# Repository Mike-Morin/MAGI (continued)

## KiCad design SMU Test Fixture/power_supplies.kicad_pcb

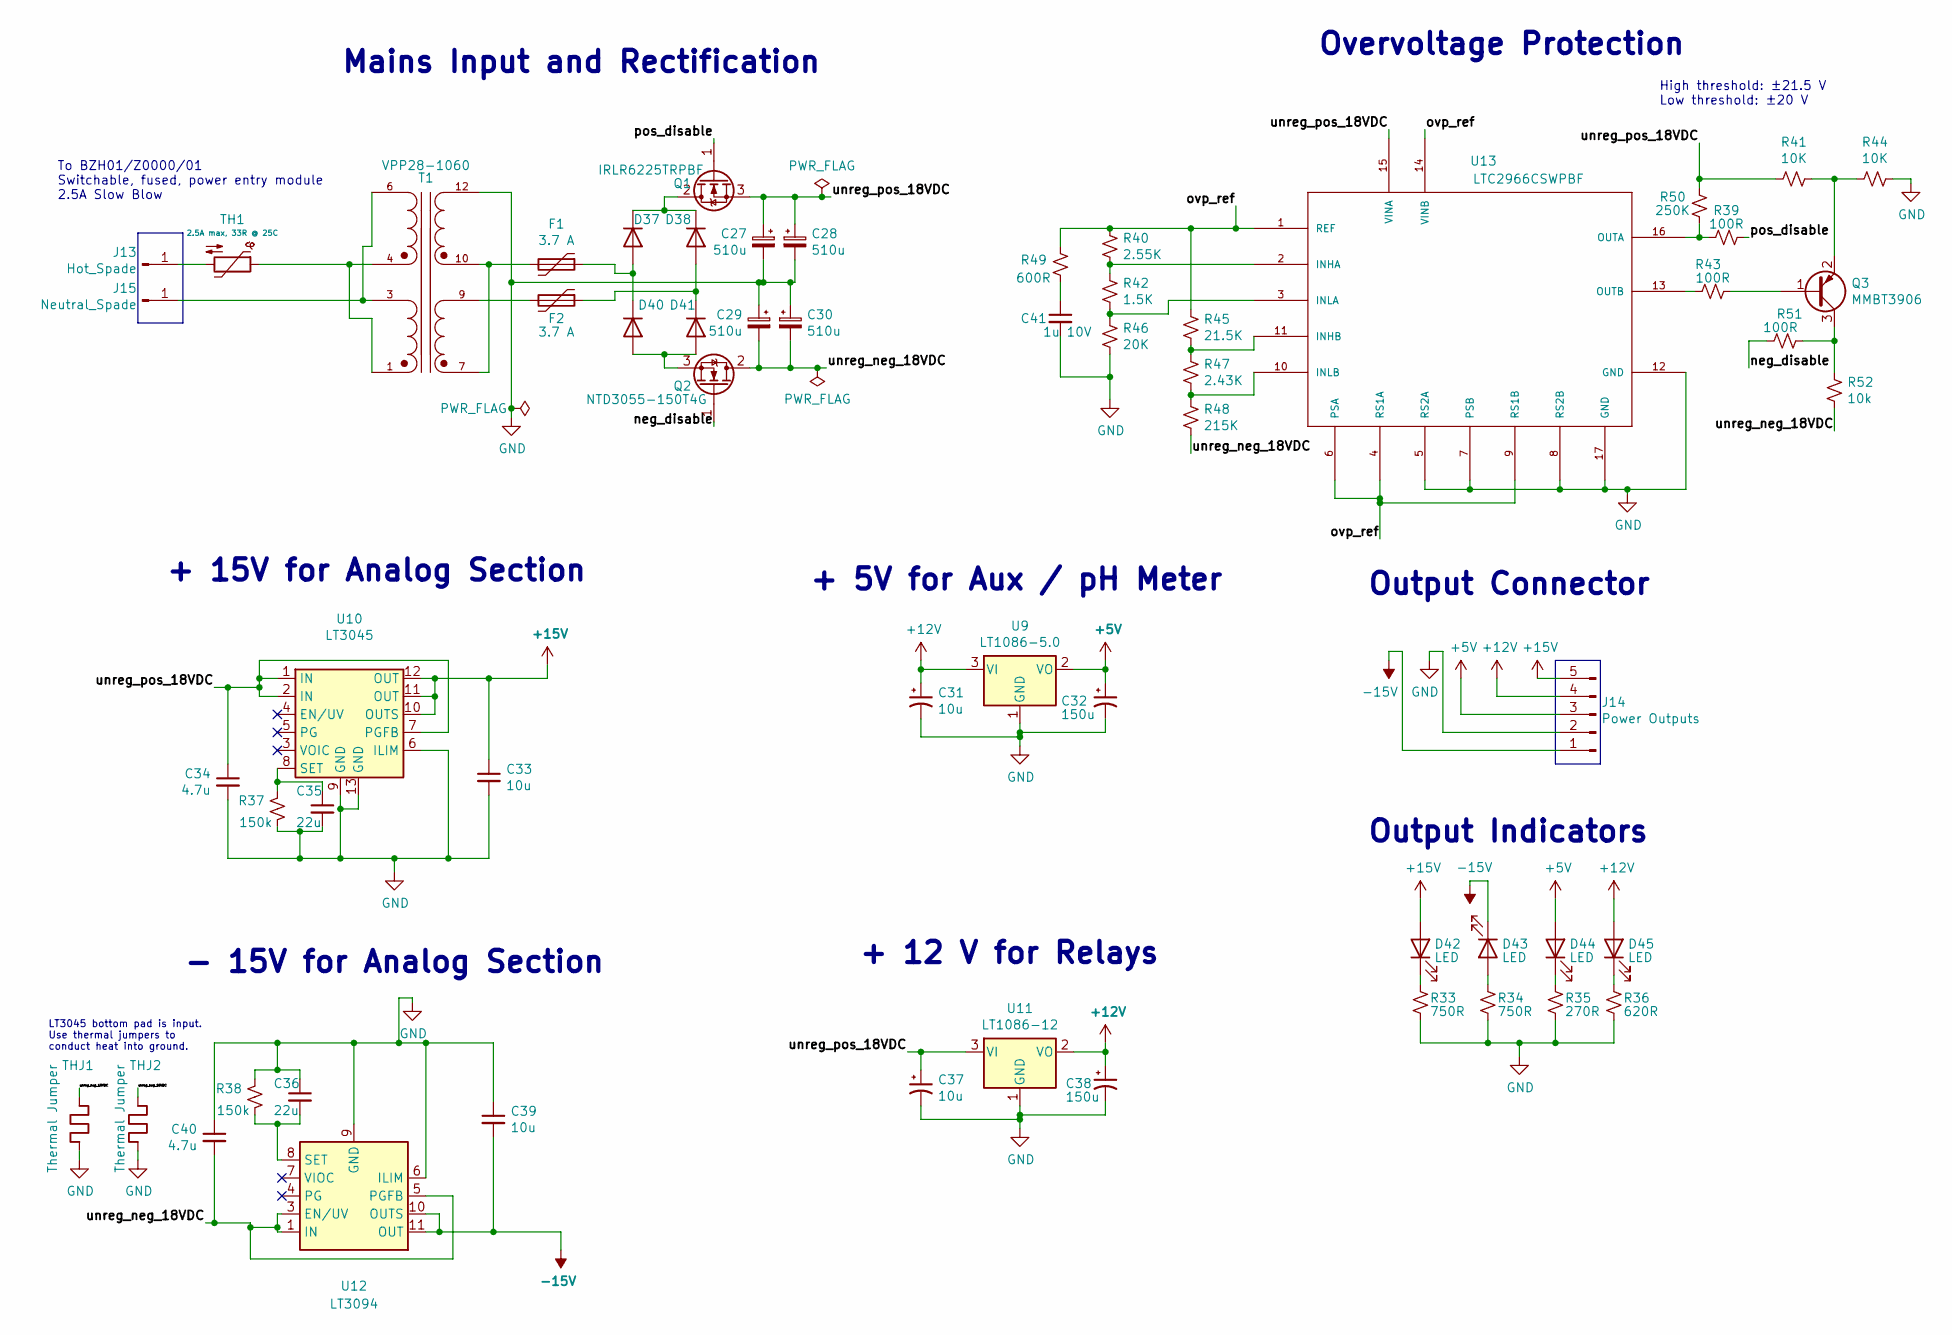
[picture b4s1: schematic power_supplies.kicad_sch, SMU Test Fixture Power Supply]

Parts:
C27, C28, C29, C30: 510u; CP_Elec_18x22
C31, C37: 10u; CP_Elec_6.3x5.8
C32, C38: 150u; CP_Elec_10x10
C33, C39: 10u; C_0805_2012Metric_Pad1.18x1.45mm_HandSolder_Kelvin
C34, C40: 4.7u; C_0805_2012Metric_Pad1.18x1.45mm_HandSolder
C35, C36: 22u; C_0805_2012Metric_Pad1.18x1.45mm_HandSolder
C41: 1u 10V; C_0603_1608Metric_Pad1.08x0.95mm_HandSolder
D37, D38, D40, D41: D; TO-263-2
D42, D43, D44, D45: LED; LED_D3.0mm_Horizontal_O6.35mm_Z2.0mm
F1, F2: 3.7 A; Fuse_2920_7451Metric_Pad2.10x5.45mm_HandSolder
J13: Hot_Spade; p250_spade
J14: Power Outputs; PinHeader_1x05_P2.54mm_Horizontal
J15: Neutral_Spade; p250_spade
Q1: IRLR6225TRPBF; TO-252-2
Q2: NTD3055-150T4G; TO-252-2
Q3: MMBT3906; SOT-23
R33, R34: 750R; R_0805_2012Metric_Pad1.20x1.40mm_HandSolder
R35: 270R; R_0805_2012Metric_Pad1.20x1.40mm_HandSolder
R36: 620R; R_0805_2012Metric_Pad1.20x1.40mm_HandSolder
R37, R38: 150k; R_0805_2012Metric_Pad1.20x1.40mm_HandSolder
R39, R43, R51: 100R; R_0603_1608Metric_Pad0.98x0.95mm_HandSolder
R40: 2.55K; R_0603_1608Metric_Pad0.98x0.95mm_HandSolder
R41, R44: 10K; R_0603_1608Metric_Pad0.98x0.95mm_HandSolder
R42: 1.5K; R_0603_1608Metric_Pad0.98x0.95mm_HandSolder
R45: 21.5K; R_0603_1608Metric_Pad0.98x0.95mm_HandSolder
R46: 20K; R_0603_1608Metric_Pad0.98x0.95mm_HandSolder
R47: 2.43K; R_0603_1608Metric_Pad0.98x0.95mm_HandSolder
R48: 215K; R_0603_1608Metric_Pad0.98x0.95mm_HandSolder
R49: 600R; R_0603_1608Metric_Pad0.98x0.95mm_HandSolder
R50: 250K; R_0603_1608Metric_Pad0.98x0.95mm_HandSolder
R52: 10k; R_0603_1608Metric_Pad0.98x0.95mm_HandSolder
T1: VPP28-1060; XFMR_VPP28-1060
TH1: 2.5A max, 33R @ 25C; NTC d=15 p=7p5mm w=7mm
THJ1, THJ2: Thermal Jumper; C_0805_2012Metric_Pad1.18x1.45mm_HandSolder
U9: LT1086-5.0; TO-220-3_Vertical
U10: LT3045; MSOP-12-1EP_3x4mm_P0.65mm_EP1.65x2.85mm
U11: LT1086-12; TO-220-3_Vertical
U12: LT3094; MSOP-12-1EP_3x4mm_P0.65mm_EP1.65x2.85mm
U13: LTC2966CSWPBF; QFN-16-1EP_3x3mm_P0.5mm_EP1.45x1.45mm; MANUFACTURER_PART_NUMBER ltc2966csw#pbf

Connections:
+5V: C32.1, D44.2 (A), J14.3, U9.2 (VO)
+12V: C31.1, C38.1, D45.2 (A), J14.4, U9.3 (VI), U11.2 (VO)
+15V: C33.1, D42.2 (A), J14.5, U10.10 (OUTS), U10.11 (OUT), U10.12 (OUT)
-15V: C39.2, D43.1 (K), J14.1, U12.10 (OUTS), U12.11 (OUT), U12.12 (OUT)
/neg_disable: Q2.1 (G), R51.2
/ovp_ref: R40.1, R45.1, R49.1, U13.1 (REF), U13.4 (RS1A), U13.6 (PSA), U13.9 (RS1B), U13.14 (VINB)
/pos_disable: Q1.1 (G), R39.1
/unreg_neg_18VDC: C29.2, C30.2, C40.2, Q2.2 (D), R48.2, R52.2, THJ1.1, THJ2.1, U12.1 (IN), U12.2 (IN), U12.3 (EN/UV), U12.5 (PGFB), U12.13 (IN)
/unreg_pos_18VDC: C27.1, C28.1, C34.1, C37.1, Q1.3 (S), R41.2, R50.1, U10.1 (IN), U10.2 (IN), U10.7 (PGFB), U11.3 (VI), U13.15 (VINA)
GND: C27.2, C28.2, C29.1, C30.1, C31.2, C32.2, C33.2, C34.2, C35.2, C36.1, C37.2, C38.2, C39.1, C40.1, C41.2, J14.2, R33.2, R34.2, R35.2, R36.2, R37.2, R38.1, R44.1, R46.2, T1.12, THJ1.2, THJ2.2, U9.1 (GND), U10.6 (ILIM), U10.9 (GND), U10.13 (GND), U11.1 (GND), U12.6 (ILIM), U12.9 (GND), U13.5 (RS2A), U13.7 (PSB), U13.8 (RS2B), U13.12 (GND), U13.17 (GND)
unnamed: C35.1, R37.1, U10.8 (SET)
unnamed: C36.2, R38.2, U12.8 (SET)
unnamed: C41.1, R49.2
unnamed: D37.1 (K), D38.1 (K), Q1.2 (D)
unnamed: D37.2 (A), D40.1 (K), F1.1
unnamed: D38.2 (A), D41.1 (K), F2.1
unnamed: D40.2 (A), D41.2 (A), Q2.3 (S)
unnamed: D42.1 (K), R33.1
unnamed: D43.2 (A), R34.1
unnamed: D44.1 (K), R35.1
unnamed: D45.1 (K), R36.1
unnamed: F1.2, T1.7, T1.10
unnamed: F2.2, T1.9
unnamed: J13.1, TH1.2
unnamed: J15.1, T1.3, T1.6
unnamed: Q3.1 (B), R43.2
unnamed: Q3.2 (E), R41.1, R44.2
unnamed: Q3.3 (C), R51.1, R52.1
unnamed: R39.2, R50.2, U13.16 (OUTA)
unnamed: R40.2, R42.1, U13.2 (INHA)
unnamed: R42.2, R46.1, U13.3 (INLA)
unnamed: R43.1, U13.13 (OUTB)
unnamed: R45.2, R47.1, U13.11 (INHB)
unnamed: R47.2, R48.1, U13.10 (INLB)
unnamed: T1.1, T1.4, TH1.1

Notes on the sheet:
LT3045 bottom pad is input. Use thermal jumpers to conduct heat into ground.
Overvoltage Protection
+ 5V for Aux / pH Meter
Output Indicators
To BZH01/Z0000/01 Switchable, fused, power entry module 2.5A Slow Blow
- 15V for Analog Section
Mains Input and Rectification
+ 12 V for Relays
+ 15V for Analog Section
Output Connector
High threshold: ±21.5 V Low threshold: ±20 V

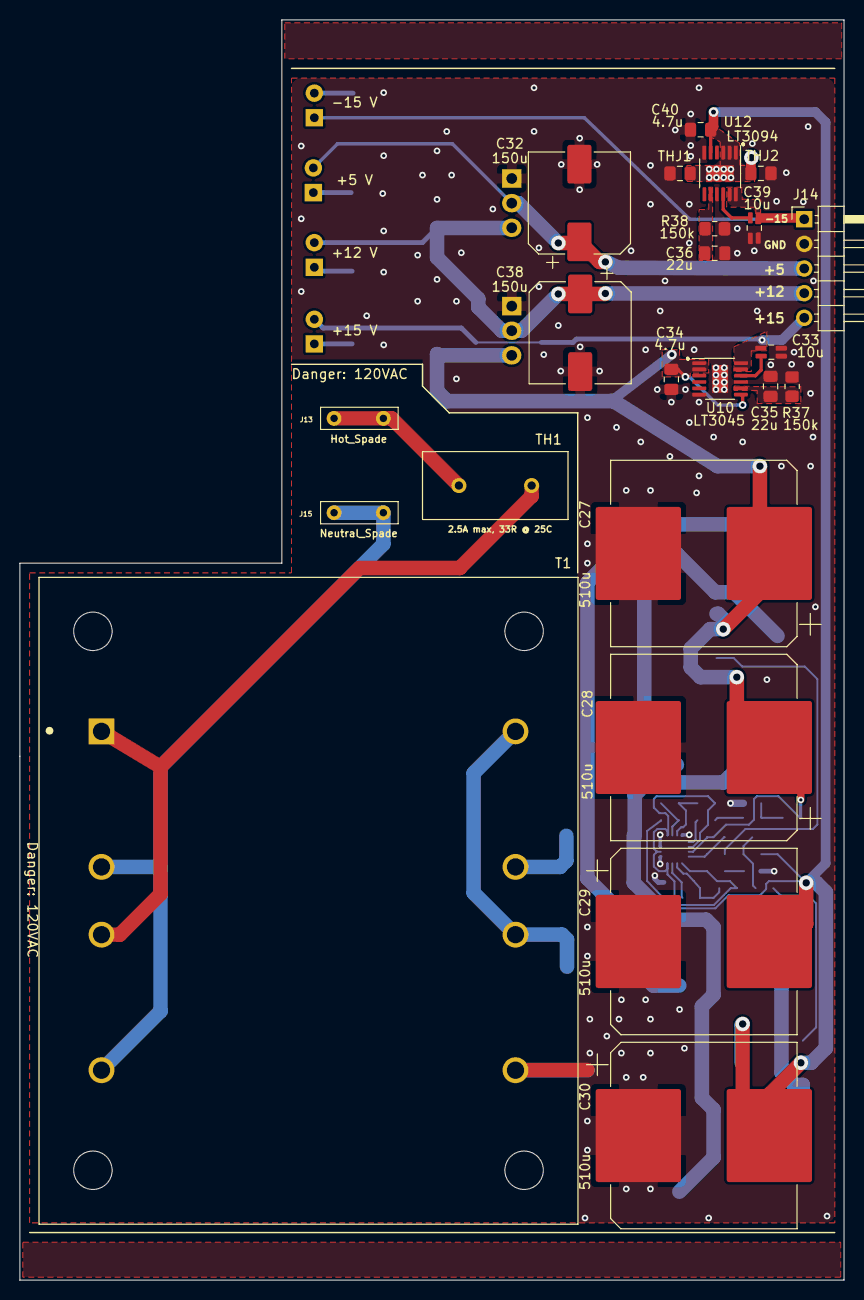
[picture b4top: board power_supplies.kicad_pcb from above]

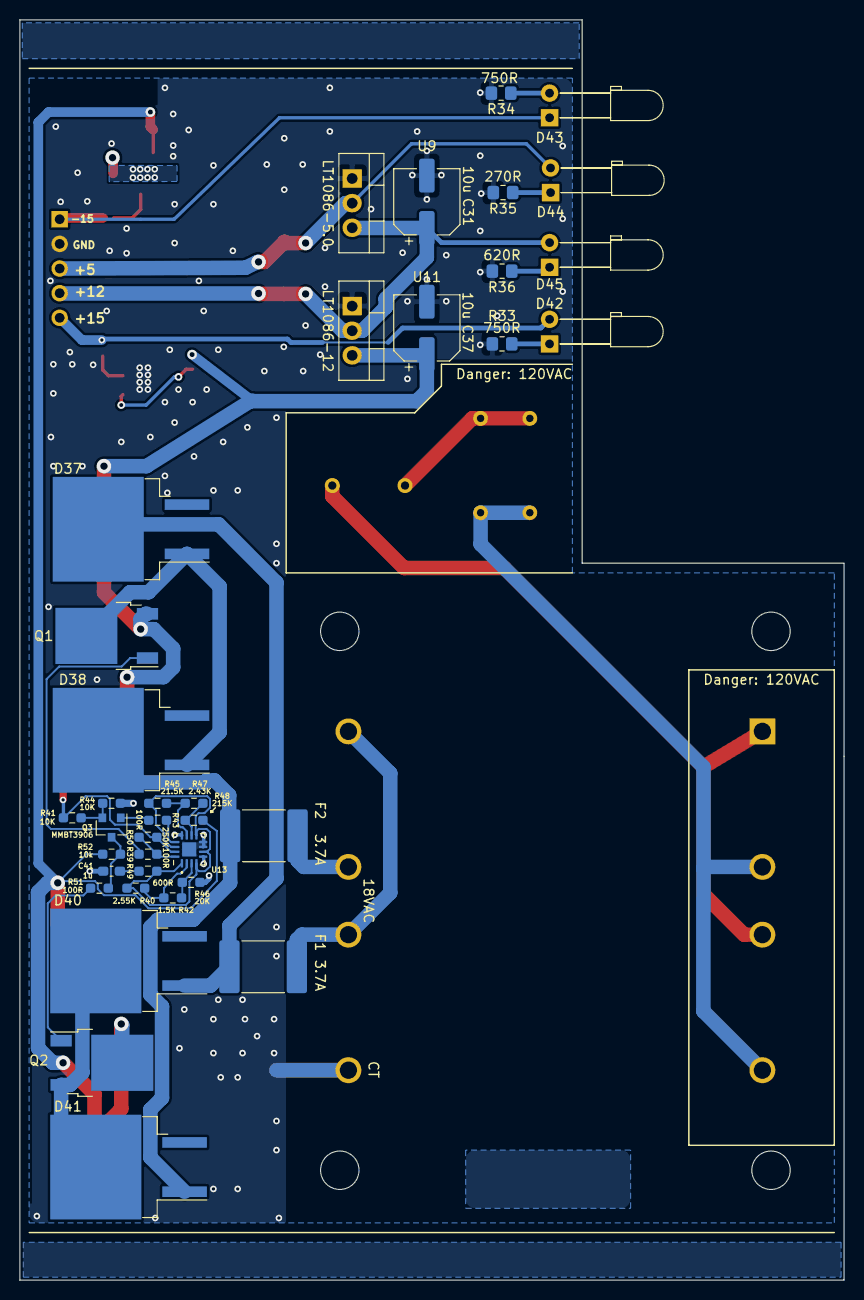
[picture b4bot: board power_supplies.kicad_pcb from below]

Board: 2 copper layers, 84.9 x 129.9 mm, 60 parts (37 on the bottom side), 35 nets.

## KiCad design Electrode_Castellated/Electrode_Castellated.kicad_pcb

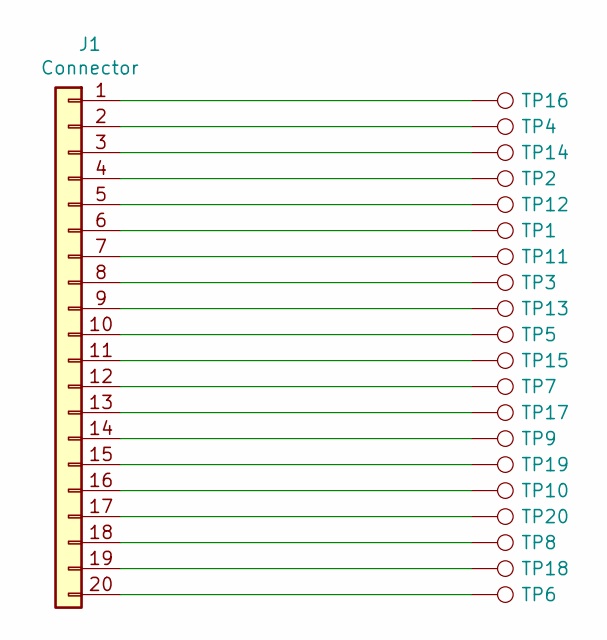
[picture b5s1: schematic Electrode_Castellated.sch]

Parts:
J1: Connector; Millmax Pad Contacts
TP1: 6; TestPoint_THTPad_D2.0mm_Drill1.0mm
TP2: 4; TestPoint_THTPad_D2.0mm_Drill1.0mm
TP3: 8; TestPoint_THTPad_D2.0mm_Drill1.0mm
TP4: 2; TestPoint_THTPad_D2.0mm_Drill1.0mm
TP5: 10; TestPoint_THTPad_D2.0mm_Drill1.0mm
TP6: 30; TestPoint_THTPad_D2.0mm_Drill1.0mm
TP7: 12; TestPoint_THTPad_D2.0mm_Drill1.0mm
TP8: 18; TestPoint_THTPad_D2.0mm_Drill1.0mm
TP9: 14; TestPoint_THTPad_D2.0mm_Drill1.0mm
TP10: 16; TestPoint_THTPad_D2.0mm_Drill1.0mm
TP11: 7; TestPoint_THTPad_D2.0mm_Drill1.0mm
TP12: 5; TestPoint_THTPad_D2.0mm_Drill1.0mm
TP13: 9; TestPoint_THTPad_D2.0mm_Drill1.0mm
TP14: 3; TestPoint_THTPad_D2.0mm_Drill1.0mm
TP15: 11; TestPoint_THTPad_D2.0mm_Drill1.0mm
TP16: 1; TestPoint_THTPad_D2.0mm_Drill1.0mm
TP17: 13; TestPoint_THTPad_D2.0mm_Drill1.0mm
TP18: 19; TestPoint_THTPad_D2.0mm_Drill1.0mm
TP19: 15; TestPoint_THTPad_D2.0mm_Drill1.0mm
TP20: 17; TestPoint_THTPad_D2.0mm_Drill1.0mm

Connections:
unnamed: J1.1, TP16.1
unnamed: J1.2, TP4.1
unnamed: J1.3, TP14.1
unnamed: J1.4, TP2.1
unnamed: J1.5, TP12.1
unnamed: J1.6, TP1.1
unnamed: J1.7, TP11.1
unnamed: J1.8, TP3.1
unnamed: J1.9, TP13.1
unnamed: J1.10, TP5.1
unnamed: J1.11, TP15.1
unnamed: J1.12, TP7.1
unnamed: J1.13, TP17.1
unnamed: J1.14, TP9.1
unnamed: J1.15, TP19.1
unnamed: J1.16, TP10.1
unnamed: J1.17, TP20.1
unnamed: J1.18, TP8.1
unnamed: J1.19, TP18.1
unnamed: J1.20, TP6.1

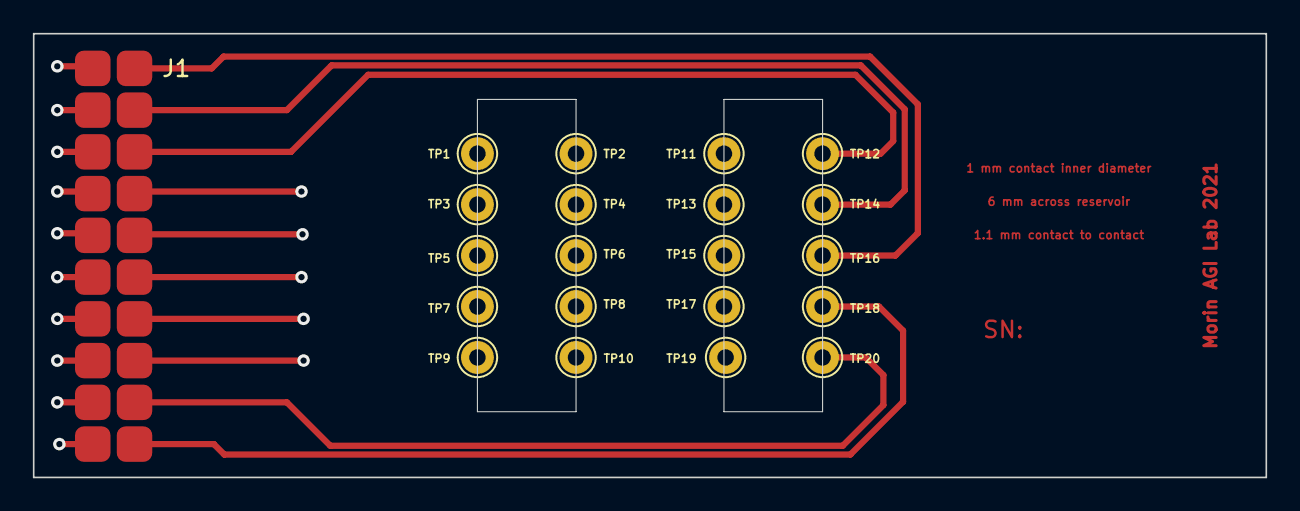
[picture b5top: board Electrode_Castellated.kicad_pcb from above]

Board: 4 copper layers, 75.0 x 27.0 mm, 21 parts (0 on the bottom side), 20 nets.

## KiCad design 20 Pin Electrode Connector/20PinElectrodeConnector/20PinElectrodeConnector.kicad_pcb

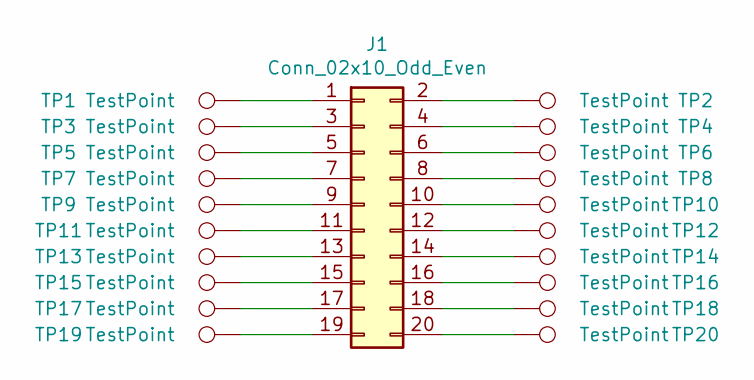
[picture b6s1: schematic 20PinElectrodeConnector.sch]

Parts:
J1: Conn_02x10_Odd_Even; Millimax_817-22-020-30-001101
TP1, TP2, TP3, TP4, TP5, TP6, TP7, TP8, TP9, TP10, TP11, TP12, TP13, TP14, TP15, TP16, TP17, TP18, TP19, TP20: TestPoint; SolderWire-0.25sqmm_1x01_D0.65mm_OD2mm

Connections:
unnamed: J1.1, TP1.1
unnamed: J1.2, TP2.1
unnamed: J1.3, TP3.1
unnamed: J1.4, TP4.1
unnamed: J1.5, TP5.1
unnamed: J1.6, TP6.1
unnamed: J1.7, TP7.1
unnamed: J1.8, TP8.1
unnamed: J1.9, TP9.1
unnamed: J1.10, TP10.1
unnamed: J1.11, TP11.1
unnamed: J1.12, TP12.1
unnamed: J1.13, TP13.1
unnamed: J1.14, TP14.1
unnamed: J1.15, TP15.1
unnamed: J1.16, TP16.1
unnamed: J1.17, TP17.1
unnamed: J1.18, TP18.1
unnamed: J1.19, TP19.1
unnamed: J1.20, TP20.1

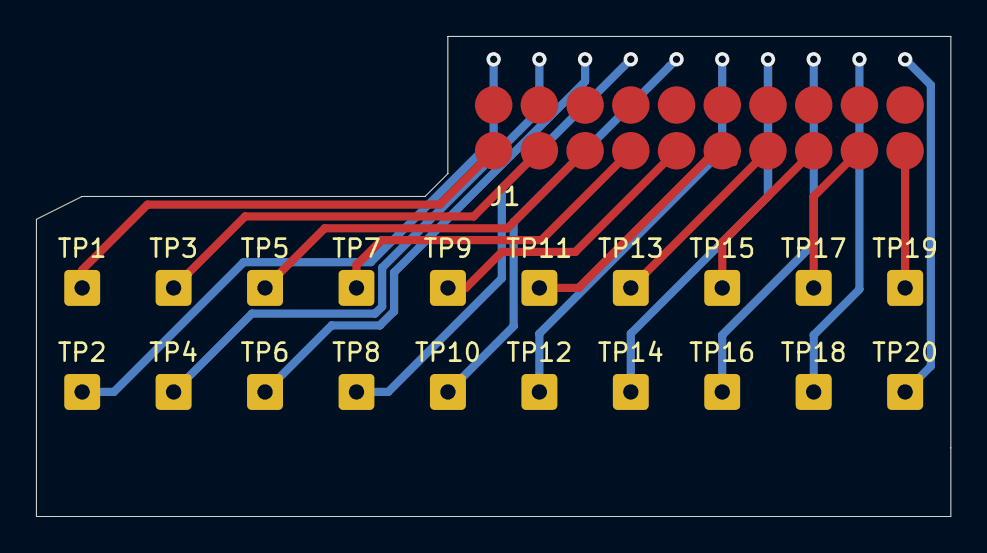
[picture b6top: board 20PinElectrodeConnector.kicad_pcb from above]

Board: 2 copper layers, 50.8 x 26.7 mm, 21 parts (0 on the bottom side), 20 nets.

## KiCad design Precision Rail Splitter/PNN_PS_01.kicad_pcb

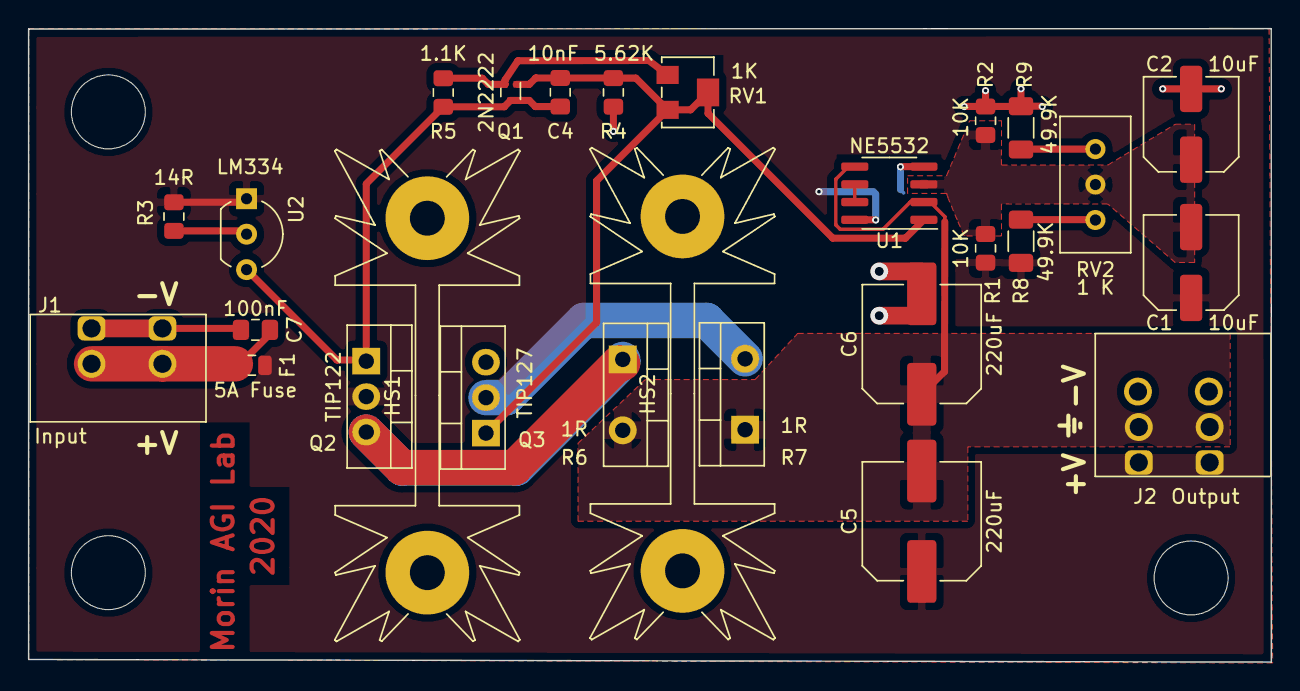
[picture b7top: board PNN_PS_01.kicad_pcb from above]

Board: 2 copper layers, 89.1 x 45.4 mm, 31 parts (1 on the bottom side), 14 nets.

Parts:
C1, C2: 10uF; C_Elec_6.3x5.8
C3, C7: 100nF; C_0805_2012Metric_Pad1.18x1.45mm_HandSolder
C4: 10nF; C_0805_2012Metric_Pad1.15x1.40mm_HandSolder
C5, C6: 220uF; C_Elec_8x10.2
F1: 5A Fuse; Fuse_0805_2012Metric
H1, H2, H3: MountingHole; MountingHole_5.3mm_M5_ISO14580
HS1, HS2: Heatsink; courtyardfix_Heatsink_Fischer_SK104-STC-STIC_35x13mm_2xDril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
J1: Input; EM274202H
J2: Output; EM274203H
Q1: 2N2222; SOT-723
Q2: TIP122; TO-220-3_Vertical
Q3: TIP127; TO-220-3_Vertical
R1, R2: 10K; R_0805_2012Metric_Pad1.15x1.40mm_HandSolder
R3: 14R; R_0805_2012Metric_Pad1.15x1.40mm_HandSolder
R4: 5.62K; R_0805_2012Metric_Pad1.15x1.40mm_HandSolder
R5: 1.1K; R_0805_2012Metric_Pad1.15x1.40mm_HandSolder
R6, R7: 1R; TO-220-2_Vertical
R8, R9: 49.9K; R_1206_3216Metric_Pad1.30x1.75mm_HandSolder
RV1: 1K; Potentiometer_Bourns_3214W_Vertical
RV2: 1 K; Potentiometer_Bourns_3296W_Vertical
U1: NE5532; SOIC-8_3.9x4.9mm_P1.27mm
U2: LM334; TO-92_Inline_Wide

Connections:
+9V: C1.1, C3.1, C5.1, F1.2, J2.1, Q2.2, R1.1, R3.1, R8.1, U1.8, U2.1
-9V: C2.2, C3.2, C6.2, C7.1, J1.1, J2.3, Q3.3, R2.2, R4.2, R9.2, U1.4
GND: C5.2, C6.1, J2.2, R6.2, R7.1, U1.2, U1.5
unnamed: C1.2, C2.1, R1.2, R2.1, RV2.2, U1.3
unnamed: C4.1, Q1.3, Q2.1, R5.1, U2.3
unnamed: C4.2, Q1.1, Q3.1, R4.1, RV1.2, RV1.3, U1.1
unnamed: C7.2, F1.1, J1.2
unnamed: Q1.2, R5.2, RV1.1
unnamed: Q2.3, R6.1
unnamed: Q3.2, R7.2
unnamed: R3.2, U2.2
unnamed: R8.2, RV2.1
unnamed: R9.1, RV2.3
unnamed: U1.6, U1.7

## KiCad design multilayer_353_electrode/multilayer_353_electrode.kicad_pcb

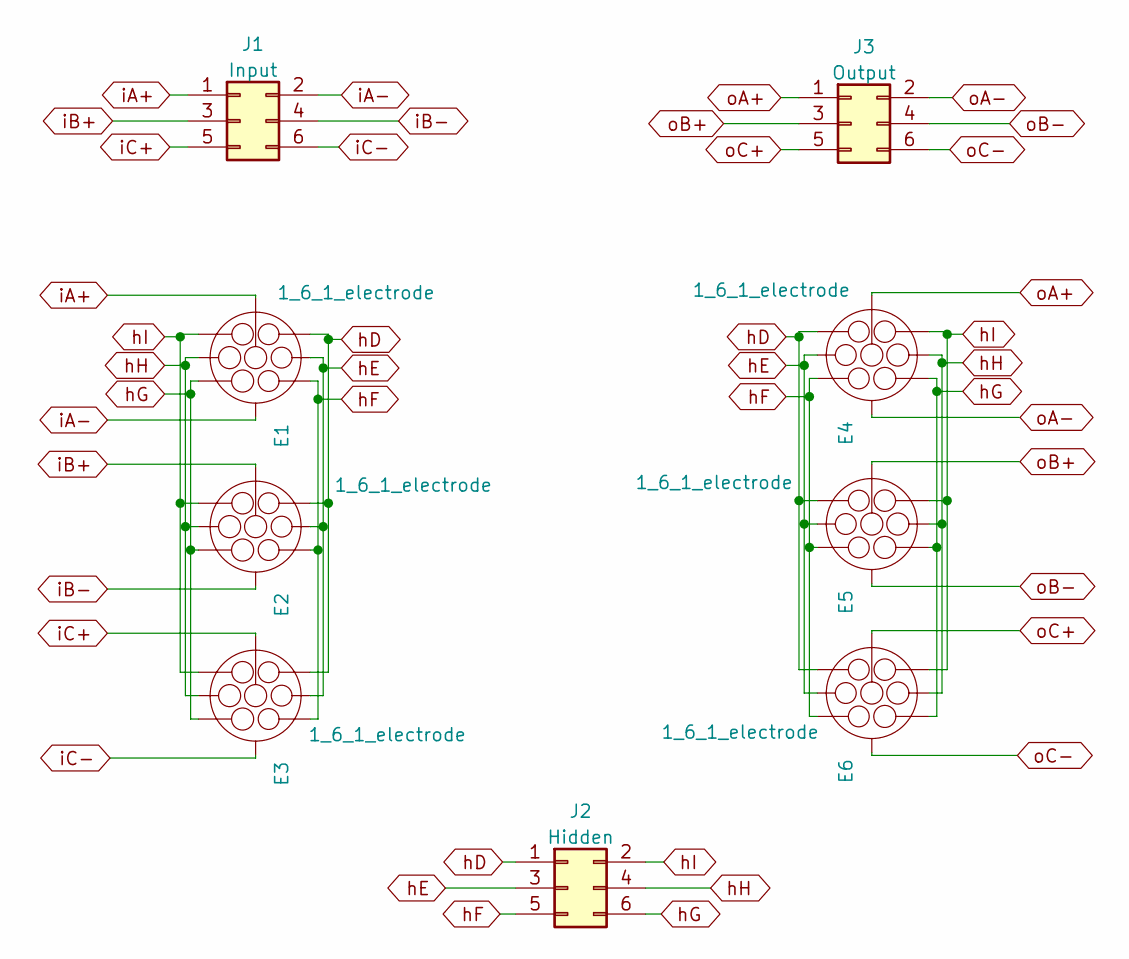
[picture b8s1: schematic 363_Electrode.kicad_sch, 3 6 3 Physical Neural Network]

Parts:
E1, E2, E3, E4, E5, E6: 1_6_1_electrode
J1: Input; PinHeader_2x03_P2.54mm_Vertical_SMD
J2: Hidden; PinHeader_2x03_P2.54mm_Vertical_SMD
J3: Output; PinHeader_2x03_P2.54mm_Vertical_SMD

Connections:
hD: E1.7 (H6), E2.7 (H6), E3.7 (H6), E4.7 (H6), E5.7 (H6), E6.7 (H6), J2.1
hE: E1.2 (H1), E2.2 (H1), E3.2 (H1), E4.2 (H1), E5.2 (H1), E6.2 (H1), J2.3
hF: E1.3 (H2), E2.3 (H2), E3.3 (H2), E4.3 (H2), E5.3 (H2), E6.3 (H2), J2.5
hG: E1.4 (H3), E2.4 (H3), E3.4 (H3), E4.4 (H3), E5.4 (H3), E6.4 (H3), J2.6
hH: E1.5 (H4), E2.5 (H4), E3.5 (H4), E4.5 (H4), E5.5 (H4), E6.5 (H4), J2.4
hI: E1.6 (H5), E2.6 (H5), E3.6 (H5), E4.6 (H5), E5.6 (H5), E6.6 (H5), J2.2
iA+: E1.1 (C), J1.1
iA-: E1.8 (R), J1.2
iB+: E2.1 (C), J1.3
iB-: E2.8 (R), J1.4
iC+: E3.1 (C), J1.5
iC-: E3.8 (R), J1.6
oA+: E4.1 (C), J3.1
oA-: E4.8 (R), J3.2
oB+: E5.1 (C), J3.3
oB-: E5.8 (R), J3.4
oC+: E6.1 (C), J3.5
oC-: E6.8 (R), J3.6

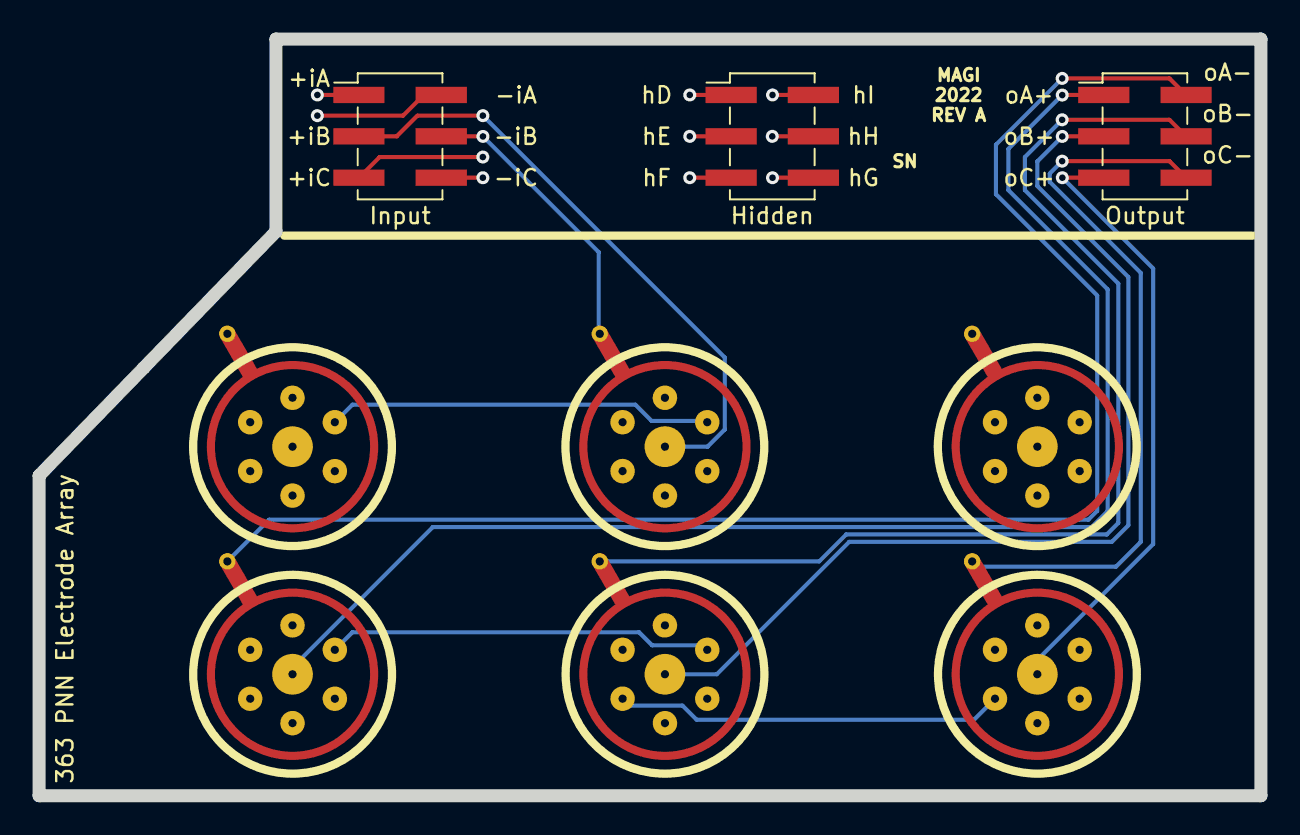
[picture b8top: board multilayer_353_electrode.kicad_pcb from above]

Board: 4 copper layers, 75.0 x 46.4 mm, 9 parts (0 on the bottom side), 18 nets.

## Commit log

2020-12-31 Moving old project into new repo
2020-12-31 Fix git submodule issue
2020-12-31 Add Zenner to keep xfrmr output below LT3045 abs max on low load, remove cap multiplier
2021-01-01 Change txfrmrs to VPP series, change 10V txfrmr to 12V to improve regulation
2021-01-02 Remove mysterious output resistors from 3094 app note.
2021-01-02 Add SCR pre-reg for +15V rail
2021-01-02 Add SCR pre-reg for -15V rail
2021-01-03 Add SCR pre-reg for 5V rail
2021-01-03 parallel fet on 5v prereg
2021-01-03 Add simulations and relay state spreadsheet
2021-01-04 Elminate extra scope cal relay, re-organize relays, re-annotate, ERC
2021-01-06 Switch to pogo pin style connector pads
2021-01-06 Move power flags
2021-01-06 Electrode connector initial commit.
2021-01-08 Conform to microscope stage bracket.
2021-01-08 Update to pogo pin pads.
2021-01-08 Add footprints for low precision/low power parts.
2021-01-10 More footprints added.
2021-01-12 NTC calulations/specs done.
2021-01-12 Footprint updates
2021-01-27 +15V LTSpice sim with pre-reg
2021-01-27 Remove edison plug from schematic, now wire holes.
2021-01-28 Comparator supply -> single-ended
2021-02-11 Switch to 28V txfrmr, nix preregs, nix 5V for AD2, switch to 12V relay power.
2021-02-20 Reannotate, power supply schematic improvements, begin power supply layout.
2021-02-27 Add .lib
2021-02-27 Change power entry module to fit enclosure.
2021-02-27 Initial component layout.
2021-03-01 Update LT3045 symbol w/ missing pins.
2021-03-01 Begin routing traces.
2021-03-02 HV and rectification sections routed.
2021-03-04 Back to kelvin connection on +-15 reg out cap
2021-03-04 Finish routing low voltage side, silkscreen
2021-03-05 Add crowbar protection for regulator inputs.
2021-03-05 Fix silks overlapping with vias.
2021-03-05 Image exports, before design review.
2021-03-05 Daisy-chain 12V->5V regs.
2021-03-05 Auto-cleanup tracks and vias
2021-03-07 Update images, fixed layers dpi.
2021-03-07 Improved crowbar performance. Posted for reddit design review.
2021-03-07 Fix silkscreen labels, add dimensions & SN
2021-03-07 Updated 3D render w/ new labels.
2021-03-11 Replace crowbar with LTC2966.
2021-03-11 Increase ptc fuse size to 3.7 A, update FPs.
2021-03-11 Switch to QFN package for LTC2966.
2021-03-16 Recalculate resistor values and select pass FETs.
2021-03-16 Route LTC2966 addition and remove pin 2 connections.
2021-03-16 Switch to QFN LTC2966 pkg.
2021-03-16 Silkscreen fixes
2021-03-17 Switch to opa1622 for greater stability.
2021-03-17 Switch to TVS flyback diodes.
2021-03-17 Design review 2
2021-03-20 Fix symbols for OPA189 and 192.
2021-03-20 Update README.md
    Grammar
2021-03-20 Schematic layout of ps section complete.
2021-03-20 Add THS2041 symbol
2021-03-20 Update README.md
    Add SMU Shunt Amp
2021-03-20 Update README.md
    Re-order, put in progress stuff at top.
2021-03-21 Schematic finished.
2021-03-21 Reduce voltage rails to +/-14V
2021-03-21 Begin PCB layout
2021-03-22 Fix null pin and add thermal pad pin to THS 4021
2021-03-22 90% finished routing PCB.
2021-03-24 PCB sent to manufacturer.
2021-03-24 BOM complete.
2021-03-24 As sent to PCB manufacture.
2021-03-24 Add part numbers to schematic.
2021-03-31 Redesign with analog switches.
2021-04-01 Add latching relay driver for integrator reset.
2021-04-02 Add analog switch power connections.
2021-04-13 Rev B changes. THS4021 footprint fix, nulling circuit corrections, gnd tp cur limit.
2021-04-16 Keepout and text tweaks
2021-04-16 Add back schematic from local backup.
2021-05-05 Add THS3092 symbol
2021-05-05 New composite staged CFB design.
2021-05-06 PCB layout initial.
2021-05-08 More vias
2021-05-10 Add ferrites
2021-05-10 Thicken output paths, add ferrites.
2021-05-12 New layout for better signal integrity
2021-05-14 Most routing done.
2021-05-20 Before *big* OPA189 move.
2021-05-21 Rollback 189 move, tighten FB path, improve power routing.
2021-06-02 Finish layout for design review.
2021-06-03 Remove fb caps after more sims. Increase fb resistors in hs loop.
2021-06-04 Better grounding for OPA189 +V bypass
2021-07-02 Move OPA189 output to THS3092 + for stability
2021-07-08 Rev C changes, opa189 now on ths3092 +
2021-07-08 Delete .gitattributes
    Trying to get github to recognize the language...
2021-07-08 Still trying to fix linguist classification.
2021-07-08 more linguist fix attempts
2021-07-12 Add new shunt amp design to SMU schematic.
2021-07-12 Remove Simulations
2021-08-09 Fix via DRC error. Reroute protection zener.
2022-09-28 Convert to KiCad 6
2022-09-29 KiCad 6 Files with SPI additions
2022-09-29 Move bypass caps to devices
2022-09-29 Use relay for wavegen output termination.
2022-09-29 Add buffered vdut output
2022-09-29 Add measurement connections to scope inputs
2022-09-29 Updated SMU Test Fixture specs
2022-09-30 Fix grid nightmare. Begin adding bypass caps for a.switches
2022-09-30 Finish adding bypass for all a.switches
2022-09-30 Split ADGS1408 units, add switch contorl page
2022-10-01 Symbol fixes, ERC pass
2022-12-07 Update readme with 363_Electrode, PetriDish, pnn_cs_drive
2022-12-07 Fix energy decay.
2022-12-07 Add agent dictionary to dish class
2022-12-07 Move stats to dish class
2022-12-07 Move controls to agent class
2022-12-08 Move starting pos to agent, add kill
2022-12-08 Add concentration + energy and accel improvements
2022-12-08 Begin waveforms integration
2022-12-08 Move food eating to dish class
2022-12-08 Concentration as a percentage
2022-12-08 Will linguist finally listen?
2022-12-09 Concentration spike output working
2022-12-09 All waveforms IO working.
2022-12-09 Fix incorrect kill pin
2022-12-09 Code readability improvements
2022-12-09 Make sure randint arg is int
2022-12-09 Add checks for None food_locations
2022-12-09 Use TypedDict for pin assignments
2022-12-09 Iterate over items()
2022-12-09 Formatting fixes
2022-12-09 Formatting improvements
2022-12-09 Add readme
2022-12-09 Add more game info
2022-12-09 Allow running with waveforms sdk installed
2022-12-09 Add info about waveforms sdk
2022-12-09 Increase default food to 10
2022-12-09 Force >1 output values to 1
2022-12-09 Fix jitter when eating food
2022-12-17 Allow user play when no device connected
2022-12-17 Fix death glitch, add death blink
2022-12-28 Use a sane number of sig figs
